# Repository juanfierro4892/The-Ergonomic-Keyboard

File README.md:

The Ergonomic Keyboard

An split keyboard that helps you to maintain a good position while you work, play or whatever you do in a computer.

I designed this because I was tired of the back pains so I decided to design and build a keyboard that helps me to maintain a good postion.

Case:

Case with the pcb:

It is designed in Fusion 360 made to fit and protect the PCB and all of the components that conforms it
The PCB here is how it end look like designed in KiCad with a lot of patience

The schematics that shows the connection between the XIAO and the capacitors and the switches

And finally the BOM which show what are the components that I'll be using 

| Name           | Purpose                                                                                                                             | Quantity | Total Cost (USD) | Link                                                                                                                                                                                                                                                                                                                                                                                                                                                                                                                                                                                                                                                         | Distributor |
|----------------|-------------------------------------------------------------------------------------------------------------------------------------|----------|------------------|--------------------------------------------------------------------------------------------------------------------------------------------------------------------------------------------------------------------------------------------------------------------------------------------------------------------------------------------------------------------------------------------------------------------------------------------------------------------------------------------------------------------------------------------------------------------------------------------------------------------------------------------------------------|-------------|
| Keycaps        | Are the identifiers of the letters, the protector of the mechanism and they came 104 as the full keyboard keycap and they're green! | 104      | 7.51             | https://es.aliexpress.com/item/1005005259313543.html?spm=a2g0o.productlist.main.1.406a2840EprXdi&algo_pvid=e2d77f1b-31d6-4291-95c6-a2a3dbda1a63&algo_exp_id=e2d77f1b-31d6-4291-95c6-a2a3dbda1a63-0&pdp_ext_f=%7B""order""%3A""587""%2C""spu_best_type""%3A""price""%2C""eval""%3A""1""%2C""fromPage""%3A""search""%7D&pdp_npi=6%40dis%21USD%217.74%217.51%21%21%217.74%217.51%21%40210328c017805390703582664eb6bc%2112000032393281286%21sea%21CO%217499892959%21X%211%210%21n_tag%3A-29912%3Bd%3A891087ae%3Bm03_new_user%3A-29895&curPageLogUid=y6zYdip12BGX&utparam-url=scene%3Asearch%7Cquery_from%3A%7Cx_object_id%3A1005005259313543%7C_p_origin_prod%3A | Aliexpress  |
| Microcontoller | To control what happens when a switch it's pressed                                                                                  | 2        | 21.56            | https://es.aliexpress.com/item/1005006988954136.html?spm=a2g0o.productlist.main.2.22dedf4cv8Y4ug&algo_pvid=4bf7f176-8760-4cdf-bc36-e818fb07e4b4&algo_exp_id=4bf7f176-8760-4cdf-bc36-e818fb07e4b4-1&pdp_ext_f=%7B""order""%3A""1935""%2C""eval""%3A""1""%2C""fromPage""%3A""search""%7D&pdp_npi=6%40dis%21USD%2118.59%2110.78%21%21%21125.54%2172.81%21%4021030a4b17798475046056962e4dc3%2112000042942288177%21sea%21CO%210%21ABX%211%210%21n_tag%3A-29910%3Bd%3A891087ae%3Bm03_new_user%3A-29895&curPageLogUid=JEf6rNpgm6uj&utparam-url=scene%3Asearch%7Cquery_from%3A%7Cx_object_id%3A1005006988954136%7C_p_origin_prod%3A                                  | Aliexpress  |
| Switches       | Are the buttons of the keyboard, I selected 50 because there isn't less than I need                                                 | 42       | 25.86            | https://es.aliexpress.com/item/1005007917912136.html?spm=a2g0o.productlist.main.10.43b5DqsuDqsuDY&algo_pvid=d73f311a-5b80-495f-892f-7f9b9d3a948d&algo_exp_id=d73f311a-5b80-495f-892f-7f9b9d3a948d-9&pdp_ext_f=%7B""order""%3A""119""%2C""eval""%3A""1""%2C""fromPage""%3A""search""%7D&pdp_npi=6%40dis%21USD%218.75%217.94%21%21%2159.08%2153.60%21%4021033d1217798471947442073e1d27%2112000042837566043%21sea%21CO%210%21ABX%211%210%21n_tag%3A-29910%3Bd%3A891087ae%3Bm03_new_user%3A-29895&curPageLogUid=73QWeeDTUJMl&utparam-url=scene%3Asearch%7Cquery_from%3A%7Cx_object_id%3A1005007917912136%7C_p_origin_prod%3A                                     | Aliexpress  |
| PCB            | To connect all the switches ant the microcontroller                                                                                 | 5        | 35.86            | https://cart.jlcpcb.com/quote?stencilLayer=2&stencilWidth=100&stencilLength=100&stencilCounts=5&plateType=1&spm=Jlcpcb.Homepage.1010                                                                                                                                                                                                                                                                                                                                                                                                                                                                                                                         | JLCPCB      |

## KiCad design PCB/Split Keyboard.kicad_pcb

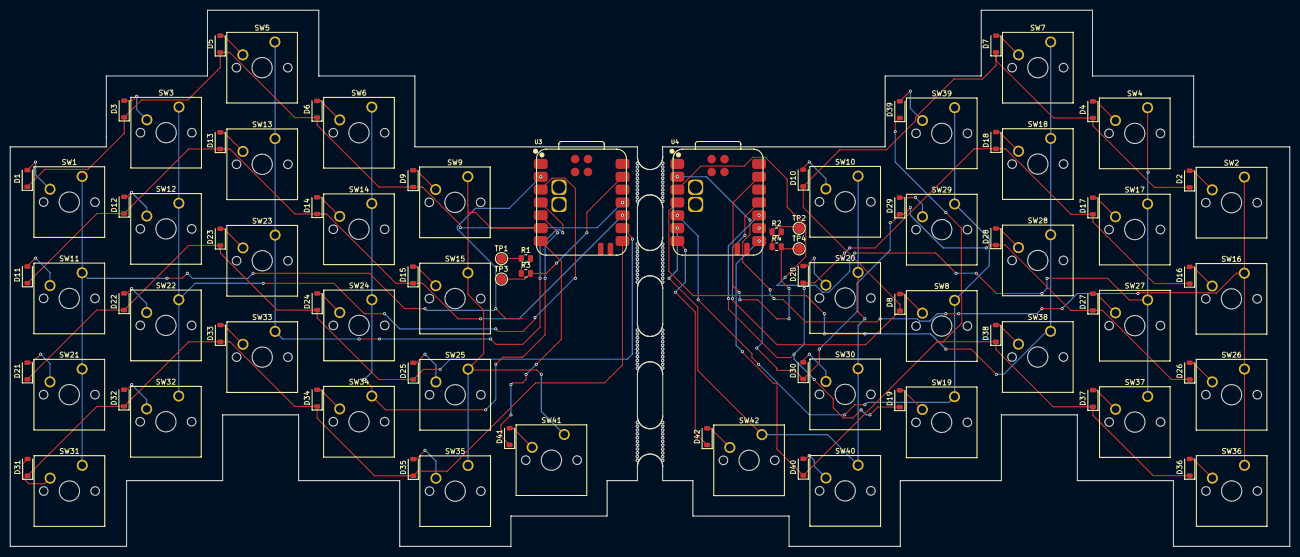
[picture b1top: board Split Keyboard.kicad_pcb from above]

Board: 2 copper layers, 253.0 x 106.0 mm, 98 parts (0 on the bottom side), 67 nets.

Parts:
D1, D2, D3, D4, D5, D6, D7, D8, D9, D10, D11, D12, D13, D14, D15, D16, D17, D18, D19, D20, D21, D22, D23, D24, D25, D26, D27, D28, D29, D30, D31, D32, D33, D34, D35, D36, D37, D38, D39, D40, D41, D42: D; D_SOD-123
H7, H8, H9, H10: MountingHole; mouse-bite-5mm-slot (1)
R1, R2: 806k; R_0805_2012Metric
R3, R4: 2M; R_0805_2012Metric
SW1, SW2, SW3, SW4, SW5, SW6, SW7, SW8, SW9, SW10, SW11, SW12, SW13, SW14, SW15, SW16, SW17, SW18, SW19, SW20, SW21, SW22, SW23, SW24, SW25, SW26, SW27, SW28, SW29, SW30, SW31, SW32, SW33, SW34, SW35, SW36, SW37, SW38, SW39, SW40, SW41, SW42: SW_Push; SW_Cherry_MX_1.00u_PCB
TP1, TP2: BAT; TestPoint_Pad_D2.0mm
TP3, TP4: GND; TestPoint_Pad_D2.0mm
U3, U4: XIAO-nRF52840-SMD; modified-XIAO-nRF52840-SMD

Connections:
/left/BT_PIN: R1.2, R3.1
/left/COL0: SW1.1, SW11.1, SW21.1, SW31.1, U3.2 (P0.03_A1_D1)
/left/COL1: SW3.1, SW12.1, SW22.1, SW32.1, U3.3 (P0.28_A2_D2)
/left/COL2: SW5.1, SW13.1, SW23.1, SW33.1, U3.4 (P0.29_A3_D3)
/left/COL3: SW6.1, SW14.1, SW24.1, SW34.1, U3.5 (P0.04_A4_D4_SDA)
/left/COL4: SW9.1, SW15.1, SW25.1, SW35.1, SW41.1, U3.6 (P0.05_A5_D5_SCL)
/left/ROW0: D1.1 (K), D3.1 (K), D5.1 (K), D6.1 (K), D9.1 (K), U3.11 (P1.15_D10_MOSI)
/left/ROW1: D11.1 (K), D12.1 (K), D13.1 (K), D14.1 (K), D15.1 (K), U3.10 (P1.14_D9_MISO)
/left/ROW2: D21.1 (K), D22.1 (K), D23.1 (K), D24.1 (K), D25.1 (K), U3.9 (P1.13_D8_SCK)
/left/ROW3: D31.1 (K), D32.1 (K), D33.1 (K), D34.1 (K), D35.1 (K), U3.8 (P1.12_D7_RX)
/left/ROW4: D41.1 (K), U3.7 (P1.11_D6_TX)
/left/VBAT: R1.1, TP1.1 (1_1)
/right/BT_PIN: R2.2, R4.1
/right/COL0: SW2.1, SW16.1, SW26.1, SW36.1, U4.2 (P0.03_A1_D1)
/right/COL1: SW4.1, SW17.1, SW27.1, SW37.1, U4.3 (P0.28_A2_D2)
/right/COL2: SW7.1, SW18.1, SW28.1, SW38.1, U4.4 (P0.29_A3_D3)
/right/COL3: SW8.1, SW19.1, SW29.1, SW39.1, U4.5 (P0.04_A4_D4_SDA)
/right/COL4: SW10.1, SW20.1, SW30.1, SW40.1, SW42.1, U4.6 (P0.05_A5_D5_SCL)
/right/ROW0: D2.1 (K), D4.1 (K), D7.1 (K), D8.1 (K), D10.1 (K), U4.11 (P1.15_D10_MOSI)
/right/ROW1: D16.1 (K), D17.1 (K), D18.1 (K), D19.1 (K), D20.1 (K), U4.10 (P1.14_D9_MISO)
/right/ROW2: D26.1 (K), D27.1 (K), D28.1 (K), D29.1 (K), D30.1 (K), U4.9 (P1.13_D8_SCK)
/right/ROW3: D36.1 (K), D37.1 (K), D38.1 (K), D39.1 (K), D40.1 (K), U4.8 (P1.12_D7_RX)
/right/ROW4: D42.1 (K), U4.7 (P1.11_D6_TX)
/right/VBAT: R2.1, TP2.1 (1_1)
GND: R3.2, R4.2, TP3.1 (1_1), TP4.1 (1_1), U3.13 (GND), U4.13 (GND)
unnamed: D1.2 (A), SW1.2
unnamed: D2.2 (A), SW2.2
unnamed: D3.2 (A), SW3.2
unnamed: D4.2 (A), SW4.2
unnamed: D5.2 (A), SW5.2
unnamed: D6.2 (A), SW6.2
unnamed: D7.2 (A), SW7.2
unnamed: D8.2 (A), SW8.2
unnamed: D9.2 (A), SW9.2
unnamed: D10.2 (A), SW10.2
unnamed: D11.2 (A), SW11.2
unnamed: D12.2 (A), SW12.2
unnamed: D13.2 (A), SW13.2
unnamed: D14.2 (A), SW14.2
unnamed: D15.2 (A), SW15.2
unnamed: D16.2 (A), SW16.2
unnamed: D17.2 (A), SW17.2
unnamed: D18.2 (A), SW18.2
unnamed: D19.2 (A), SW19.2
unnamed: D20.2 (A), SW20.2
unnamed: D21.2 (A), SW21.2
unnamed: D22.2 (A), SW22.2
unnamed: D23.2 (A), SW23.2
unnamed: D24.2 (A), SW24.2
unnamed: D25.2 (A), SW25.2
unnamed: D26.2 (A), SW26.2
unnamed: D27.2 (A), SW27.2
unnamed: D28.2 (A), SW28.2
unnamed: D29.2 (A), SW29.2
unnamed: D30.2 (A), SW30.2
unnamed: D31.2 (A), SW31.2
unnamed: D32.2 (A), SW32.2
unnamed: D33.2 (A), SW33.2
unnamed: D34.2 (A), SW34.2
unnamed: D35.2 (A), SW35.2
unnamed: D36.2 (A), SW36.2
unnamed: D37.2 (A), SW37.2
unnamed: D38.2 (A), SW38.2
unnamed: D39.2 (A), SW39.2
unnamed: D40.2 (A), SW40.2
unnamed: D41.2 (A), SW41.2
unnamed: D42.2 (A), SW42.2

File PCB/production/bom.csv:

Designator,Footprint,Quantity,Value,LCSC Part #
"D1, D10, D11, D12, D13, D14, D15, D16, D17, D18, D19, D2, D20, D21, D22, D23, D24, D25, D26, D27, D28, D29, D3, D30, D31, D32, D33, D34, D35, D36, D37, D38, D39, D4, D40, D41, D42, D5, D6, D7, D8, D9",D_SOD-123,42,D,
"R1, R2",0805,2,806k,
"R3, R4",0805,2,2M,
"SW1, SW10, SW11, SW12, SW13, SW14, SW15, SW16, SW17, SW18, SW19, SW2, SW20, SW21, SW22, SW23, SW24, SW25, SW26, SW27, SW28, SW29, SW3, SW30, SW31, SW32, SW33, SW34, SW35, SW36, SW37, SW38, SW39, SW4, SW40, SW41, SW42, SW5, SW6, SW7, SW8, SW9",SW_Cherry_MX_1.00u_PCB,42,SW_Push,
"TP1, TP2",TestPoint_Pad_D2.0mm,2,BAT,
"TP3, TP4",TestPoint_Pad_D2.0mm,2,GND,
"U3, U4",modified-XIAO-nRF52840-SMD,2,XIAO-nRF52840-SMD,

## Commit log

2026-06-14 Uploading all the files to the repository
2026-06-14 Add ergonomic keyboard details to README
    Added detailed information about the ergonomic keyboard design, including images, schematics, and a bill of materials (BOM) with component links.
2026-06-17 Update README with new images of keyboard design
    Added images of the keyboard case and PCB design.
2026-06-17 Replace old images with updated keyboard designs
    Updated images in the README to reflect new designs.
